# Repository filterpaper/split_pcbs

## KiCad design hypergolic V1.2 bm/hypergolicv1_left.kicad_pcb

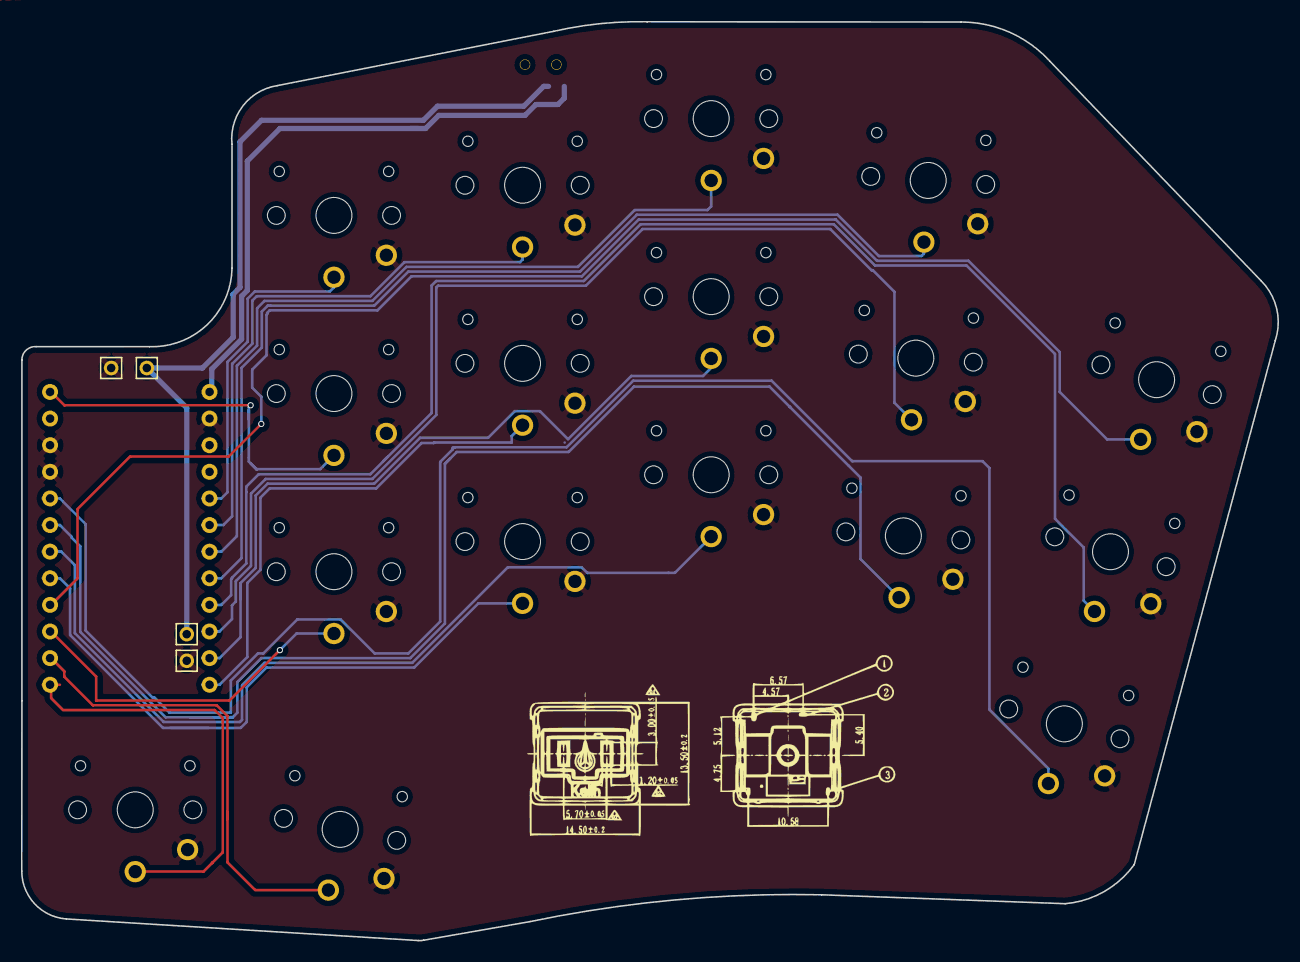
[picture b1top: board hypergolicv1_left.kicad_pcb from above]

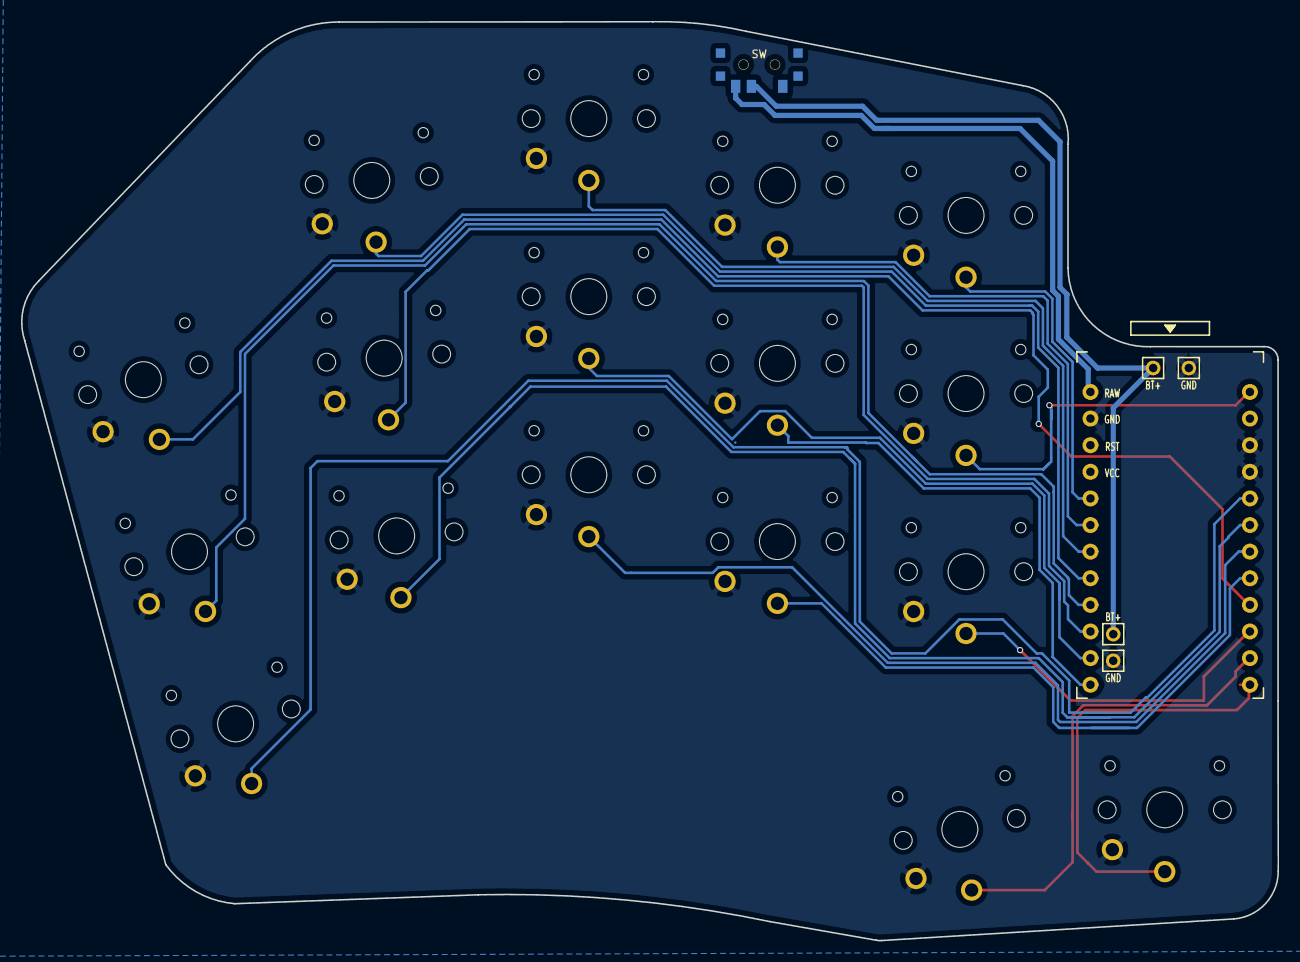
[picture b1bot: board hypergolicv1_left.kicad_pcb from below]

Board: 2 copper layers, 119.9 x 87.7 mm, 23 parts (21 on the bottom side), 20 nets.

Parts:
 : Val**; 1pin_conn
 #2: Val**; 1pin_conn
GND: MountingHole_Pad; 1pin_conn
GND#2: MountingHole_Pad; 1pin_conn
SW: SW_SPDT; SPDT_C128955
SW2, SW3, SW4, SW5, SW6, SW8, SW9, SW10, SW11, SW12, SW14, SW15, SW16, SW17, SW18, SW20, SW21: SW_Push; SW_PG1350_rev_DPB
U1: ProMicro-kbd; ProMicro_DPB

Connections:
BT+: .1, #2.1, SW.2
Switch1: SW2.1, U1.9
Switch2: SW3.1, U1.17
Switch3: SW4.1, U1.18
Switch4: SW5.1, U1.19
Switch5: SW6.1, U1.20
Switch6: SW8.1, U1.16
Switch7: SW9.1, U1.15
Switch8: SW10.1, U1.14
Switch9: SW11.1, U1.13
Switch10: SW12.1, U1.1
Switch11: SW14.1, U1.5
Switch12: SW15.1, U1.6
Switch13: SW16.1, U1.7
Switch14: SW17.1, U1.8
Switch15: SW18.1, U1.10
Switch16: SW20.1, U1.11
Switch17: SW21.1, U1.12
gnd: GND.1, GND#2.1, SW2.2, SW3.2, SW4.2, SW5.2, SW6.2, SW8.2, SW9.2, SW10.2, SW11.2, SW12.2, SW14.2, SW15.2, SW16.2, SW17.2, SW18.2, SW20.2, SW21.2, U1.3, U1.4, U1.23
raw: SW.3, U1.24

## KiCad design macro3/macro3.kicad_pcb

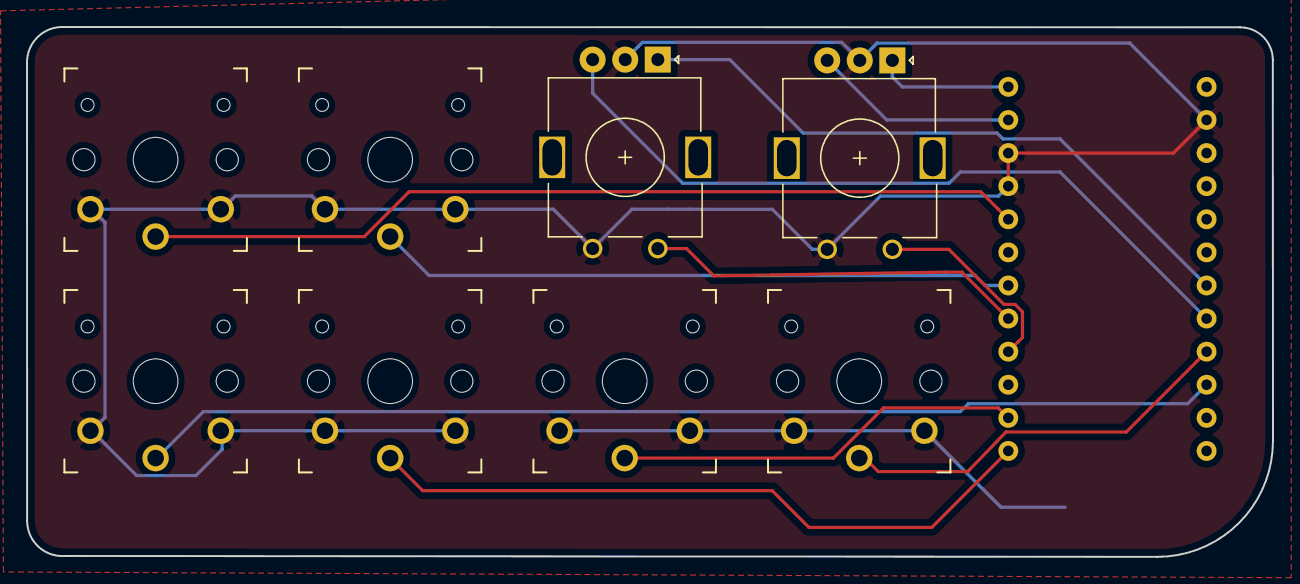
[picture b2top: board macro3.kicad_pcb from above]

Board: 2 copper layers, 95.6 x 40.7 mm, 9 parts (1 on the bottom side), 11 nets.

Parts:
 : Rotary_Encoder_Switch; RotaryEncoder_Alps_EC11E_Vertical_H20mm
 #2: Rotary_Encoder_Switch; RotaryEncoder_Alps_EC11E_Vertical_H20mm
SW1, SW2, SW5, SW6, SW7, SW8: SW_PUSH; SW_PG1350_reversible
U1: ProMicro_r; ProMicro_v3

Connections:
/SW_1: SW1.1, U1.7
/SW_5: SW5.1, U1.11
/SW_6: SW6.1, U1.12
GND: .C, #2.C, SW1.2, SW2.2, SW5.2, SW6.2, SW7.2, SW8.2, U1.3, U1.4, U1.23
unnamed: #2.A, U1.1
unnamed: #2.B, U1.2
unnamed: SW7.1, U1.5
unnamed: SW8.1, U1.15
unnamed: SW2.1, U1.16
unnamed: .B, U1.17
unnamed: .A, U1.18
